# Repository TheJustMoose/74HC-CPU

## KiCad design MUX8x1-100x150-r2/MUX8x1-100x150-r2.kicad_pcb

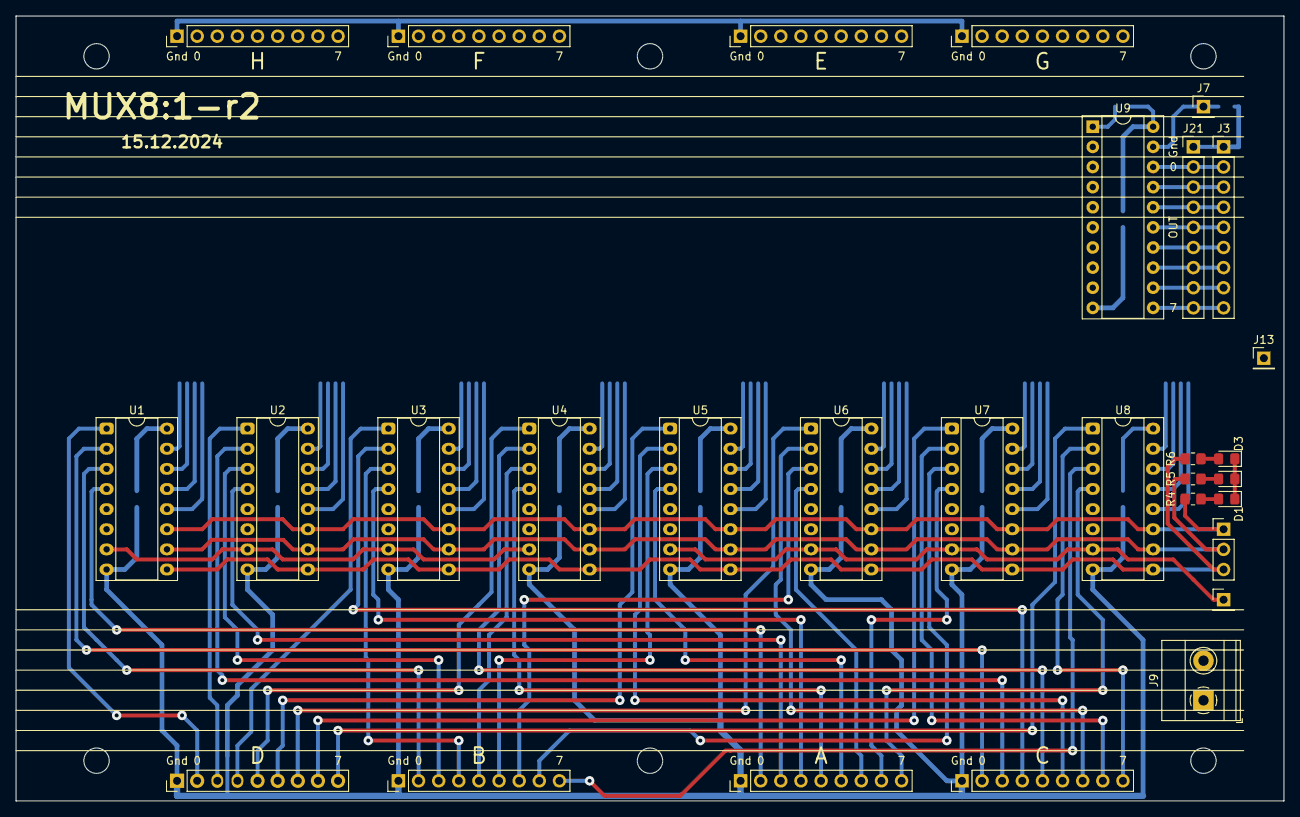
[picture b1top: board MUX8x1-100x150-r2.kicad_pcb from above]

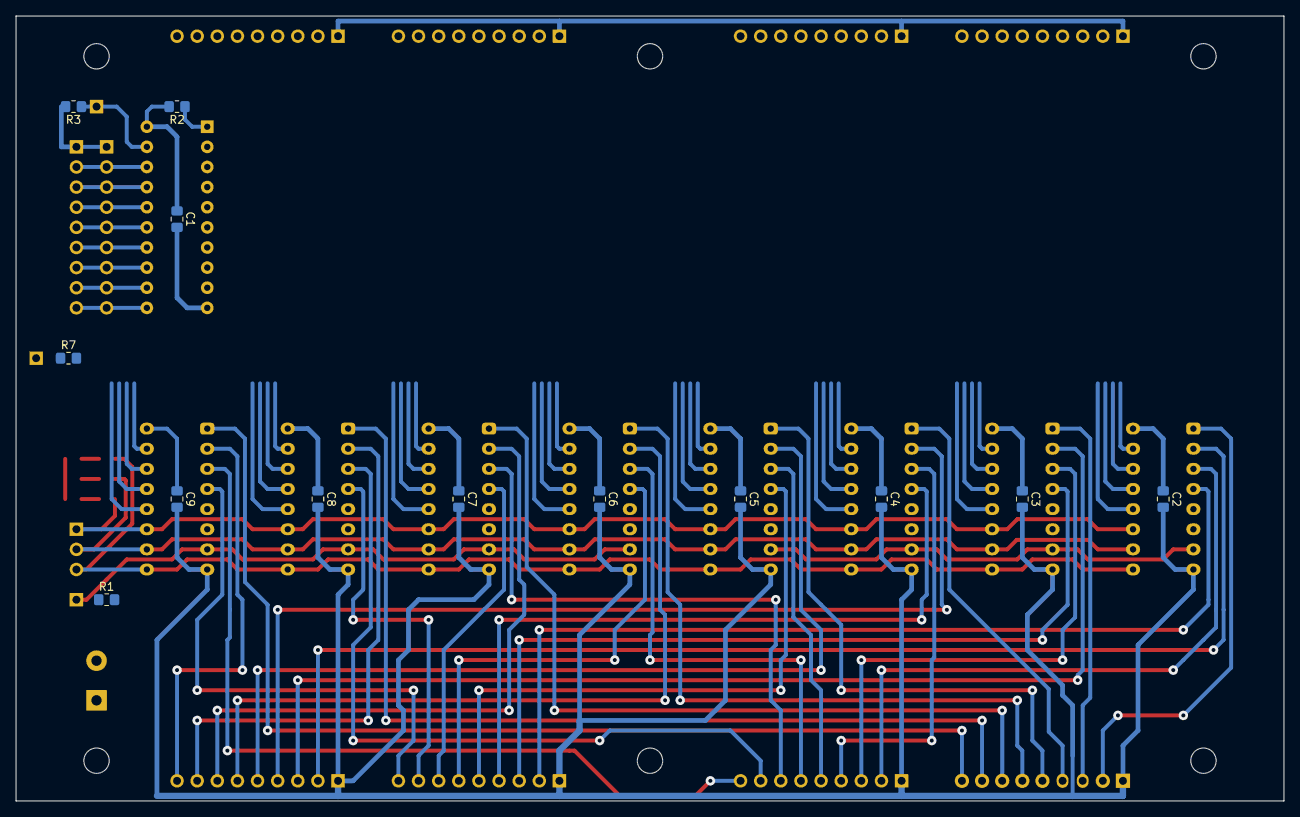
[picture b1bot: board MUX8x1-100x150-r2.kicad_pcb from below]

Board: 2 copper layers, 160.0 x 99.1 mm, 49 parts (13 on the bottom side), 92 nets.

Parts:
C1, C2, C3, C4, C5, C6, C7, C8, C9: 0.1uF; C_0805_2012Metric_Pad1.18x1.45mm_HandSolder
D1, D2, D3: LED; LED_0805_2012Metric_Pad1.15x1.40mm_HandSolder
H1, H2, H3, H4, H5, H6: MountingHole; MountingHole_3.2mm_M3
J1, J2, J3, J5, J6, J11, J12, J15, J16, J21: Conn_01x09_Male; PinHeader_1x09_P2.54mm_Vertical
J7, J13, J20: Conn_01x01_Male; PinHeader_1x01_P2.54mm_Vertical
J9: Screw_Terminal_01x02; TerminalBlock_Phoenix_MKDS-1,5-2_1x02_P5.00mm_Horizontal
J10: Conn_01x03_Male; PinHeader_1x03_P2.54mm_Vertical
R1, R2, R3, R7: 10k; R_0805_2012Metric_Pad1.20x1.40mm_HandSolder
R4, R5, R6: 1k; R_0805_2012Metric_Pad1.20x1.40mm_HandSolder
U1, U2, U3, U4, U5, U6, U7, U8: 74LS151; DIP-16_W7.62mm_Socket
U9: 74HC245; DIP-20_W7.62mm_Socket

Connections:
/A0: J1.2, U1.4
/A1: J1.3, U2.4
/A2: J1.4, U3.4
/A3: J1.5, U4.4
/A4: J1.6, U5.4
/A5: J1.7, U6.4
/A6: J1.8, U7.4
/A7: J1.9, U8.4
/B0: J5.2, U1.3
/B1: J5.3, U2.3
/B2: J5.4, U3.3
/B3: J5.5, U4.3
/B4: J5.6, U5.3
/B5: J5.7, U6.3
/B6: J5.8, U7.3
/B7: J5.9, U8.3
/BUS0: J3.2, J21.2, U9.18
/BUS1: J3.3, J21.3, U9.17
/BUS2: J3.4, J21.4, U9.16
/BUS3: J3.5, J21.5, U9.15
/BUS4: J3.6, J21.6, U9.14
/BUS5: J3.7, J21.7, U9.13
/BUS6: J3.8, J21.8, U9.12
/BUS7: J3.9, J21.9, U9.11
/C0: J11.2, U1.2
/C1: J11.3, U2.2
/C2: J11.4, U3.2
/C3: J11.5, U4.2
/C4: J11.6, U5.2
/C5: J11.7, U6.2
/C6: J11.8, U7.2
/C7: J11.9, U8.2
/D0: J15.2, U1.1
/D1: J15.3, U2.1
/D2: J15.4, U3.1
/D3: J15.5, U4.1
/D4: J15.6, U5.1
/D5: J15.7, U6.1
/D6: J15.8, U7.1
/D7: J15.9, U8.1
/E0: J2.2, U1.15
/E1: J2.3, U2.15
/E2: J2.4, U3.15
/E3: J2.5, U4.15
/E4: J2.6, U5.15
/E5: J2.7, U6.15
/E6: J2.8, U7.15
/E7: J2.9, U8.15
/F0: J6.2, U1.14
/F1: J6.3, U2.14
/F2: J6.4, U3.14
/F3: J6.5, U4.14
/F4: J6.6, U5.14
/F5: J6.7, U6.14
/F6: J6.8, U7.14
/F7: J6.9, U8.14
/G0: J12.2, U1.13
/G1: J12.3, U2.13
/G2: J12.4, U3.13
/G3: J12.5, U4.13
/G4: J12.6, U5.13
/G5: J12.7, U6.13
/G6: J12.8, U7.13
/G7: J12.9, U8.13
/H0: J16.2, U1.12
/H1: J16.3, U2.12
/H2: J16.4, U3.12
/H3: J16.5, U4.12
/H4: J16.6, U5.12
/H5: J16.7, U6.12
/H6: J16.8, U7.12
/H7: J16.9, U8.12
/O0: U1.5, U9.2
/O1: U2.5, U9.3
/O2: U3.5, U9.4
/O3: U4.5, U9.5
/O4: U5.5, U9.6
/O5: U6.5, U9.7
/O6: U7.5, U9.8
/O7: U8.5, U9.9
/S0: J10.1, R4.2, U1.11, U2.11, U3.11, U4.11, U5.11, U6.11, U7.11, U8.11
/S1: J10.2, R5.2, U1.10, U2.10, U3.10, U4.10, U5.10, U6.10, U7.10, U8.10
/S2: J10.3, R6.2, U1.9, U2.9, U3.9, U4.9, U5.9, U6.9, U7.9, U8.9
/~EH: J20.1, R1.1, U5.7, U6.7, U7.7, U8.7
/~EL: J13.1, R7.1, U1.7, U2.7, U3.7, U4.7
/~OE: J7.1, R3.1, U9.19
GND: C1.2, C2.2, C3.2, C4.2, C5.2, C6.2, C7.2, C8.2, C9.2, D1.1, D2.1, D3.1, J1.1, J2.1, J3.1, J5.1, J6.1, J9.2, J11.1, J12.1, J15.1, J16.1, J21.1, R1.2, R3.2, R7.2, U1.8, U2.8, U3.8, U4.8, U5.8, U6.8, U7.8, U8.8, U9.10
unnamed: D1.2, R4.1
unnamed: D2.2, R5.1
unnamed: D3.2, R6.1
unnamed: R2.1, U9.1
VCC: C1.1, C2.1, C3.1, C4.1, C5.1, C6.1, C7.1, C8.1, C9.1, J9.1, R2.2, U1.16, U2.16, U3.16, U4.16, U5.16, U6.16, U7.16, U8.16, U9.20

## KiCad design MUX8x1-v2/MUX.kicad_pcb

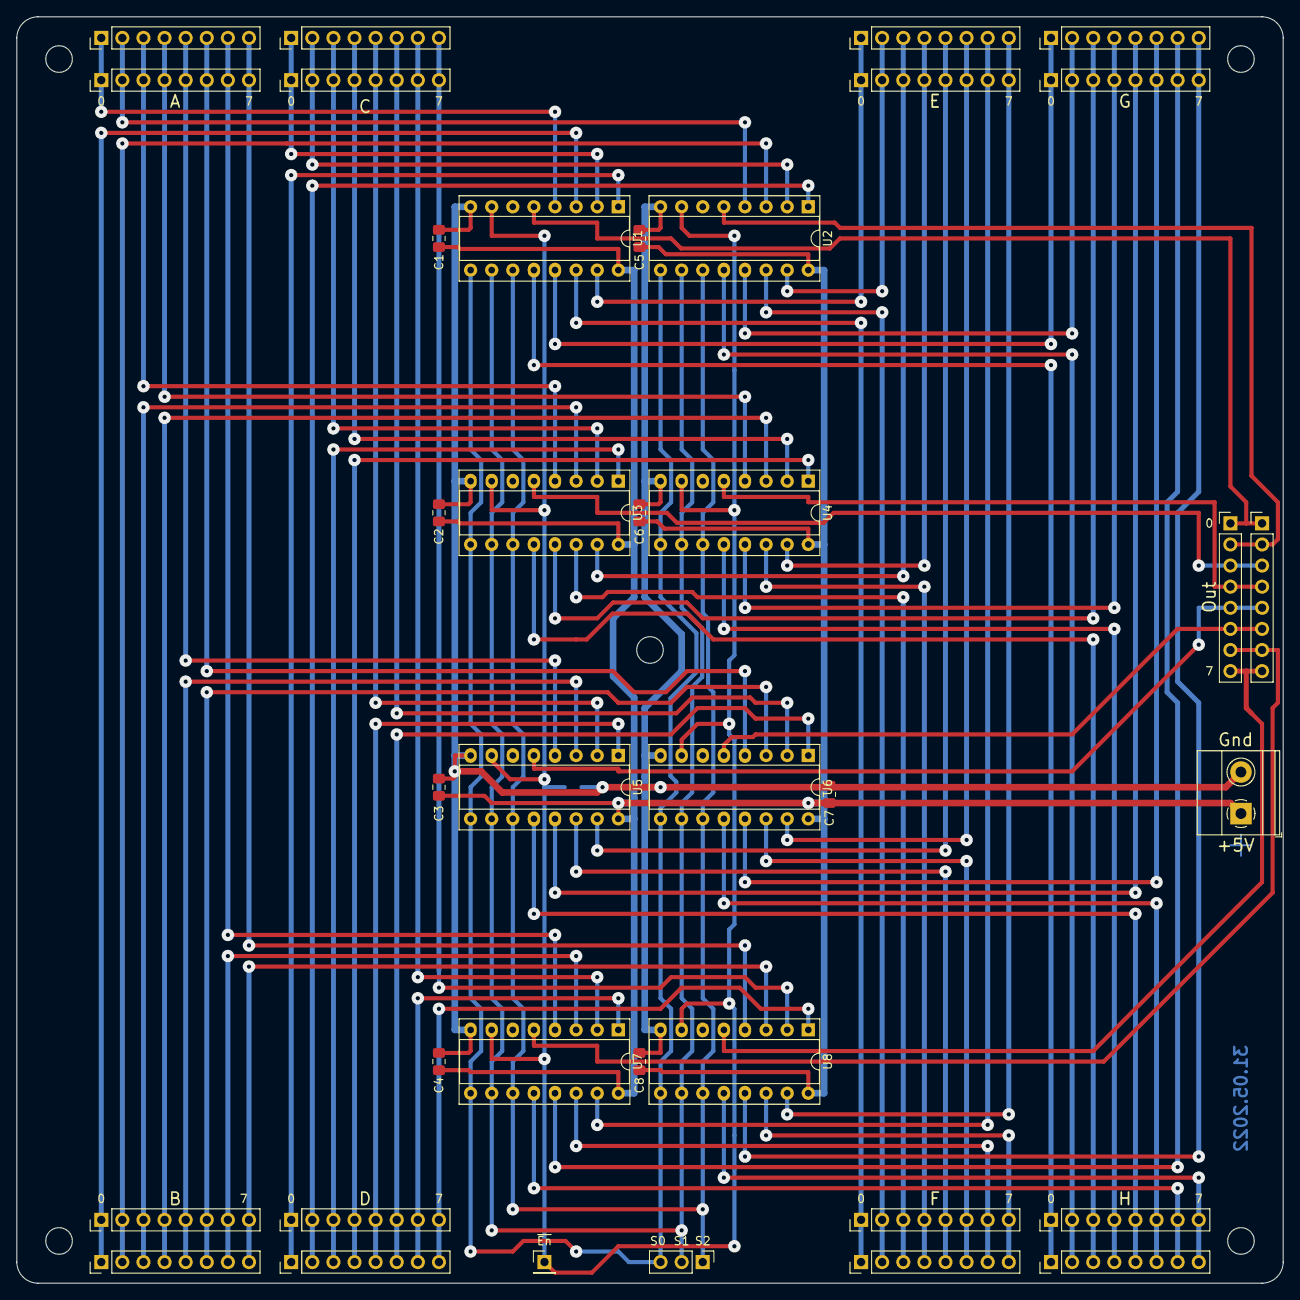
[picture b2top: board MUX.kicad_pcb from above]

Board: 2 copper layers, 152.4 x 152.4 mm, 43 parts (1 on the bottom side), 78 nets.

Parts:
C1, C2, C3, C4, C5, C6, C7, C8: 0.1uF; C_0805_2012Metric_Pad1.18x1.45mm_HandSolder
H1, H2, H3, H4, H5: MountingHole; MountingHole_3.2mm_M3
J1, J2, J3, J4, J5, J6, J7, J8, J11, J12, J13, J14, J15, J16, J17, J18, J19, J21: Conn_01x08_Male; PinHeader_1x08_P2.54mm_Vertical
J9: Screw_Terminal_01x02; TerminalBlock_Phoenix_MKDS-1,5-2_1x02_P5.00mm_Horizontal
J10: Conn_01x03_Male; PinHeader_1x03_P2.54mm_Vertical
J20: Conn_01x01_Male; PinHeader_1x01_P2.54mm_Vertical
R1: 10k; R_0805_2012Metric_Pad1.20x1.40mm_HandSolder
U1, U2, U3, U4, U5, U6, U7, U8: 74LS151; DIP-16_W7.62mm_Socket

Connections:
/A0: J1.1, J12.1, U1.4
/A1: J1.2, J12.2, U2.4
/A2: J1.3, J12.3, U3.4
/A3: J1.4, J12.4, U4.4
/A4: J1.5, J12.5, U5.4
/A5: J1.6, J12.6, U6.4
/A6: J1.7, J12.7, U7.4
/A7: J1.8, J12.8, U8.4
/B0: J3.1, J14.1, U1.3
/B1: J3.2, J14.2, U2.3
/B2: J3.3, J14.3, U3.3
/B3: J3.4, J14.4, U4.3
/B4: J3.5, J14.5, U5.3
/B5: J3.6, J14.6, U6.3
/B6: J3.7, J14.7, U7.3
/B7: J3.8, J14.8, U8.3
/C0: J5.1, J16.1, U1.2
/C1: J5.2, J16.2, U2.2
/C2: J5.3, J16.3, U3.2
/C3: J5.4, J16.4, U4.2
/C4: J5.5, J16.5, U5.2
/C5: J5.6, J16.6, U6.2
/C6: J5.7, J16.7, U7.2
/C7: J5.8, J16.8, U8.2
/D0: J7.1, J18.1, U1.1
/D1: J7.2, J18.2, U2.1
/D2: J7.3, J18.3, U3.1
/D3: J7.4, J18.4, U4.1
/D4: J7.5, J18.5, U5.1
/D5: J7.6, J18.6, U6.1
/D6: J7.7, J18.7, U7.1
/D7: J7.8, J18.8, U8.1
/E0: J2.1, J13.1, U1.15
/E1: J2.2, J13.2, U2.15
/E2: J2.3, J13.3, U3.15
/E3: J2.4, J13.4, U4.15
/E4: J2.5, J13.5, U5.15
/E5: J2.6, J13.6, U6.15
/E6: J2.7, J13.7, U7.15
/E7: J2.8, J13.8, U8.15
/F0: J4.1, J15.1, U1.14
/F1: J4.2, J15.2, U2.14
/F2: J4.3, J15.3, U3.14
/F3: J4.4, J15.4, U4.14
/F4: J4.5, J15.5, U5.14
/F5: J4.6, J15.6, U6.14
/F6: J4.7, J15.7, U7.14
/F7: J4.8, J15.8, U8.14
/G0: J6.1, J17.1, U1.13
/G1: J6.2, J17.2, U2.13
/G2: J6.3, J17.3, U3.13
/G3: J6.4, J17.4, U4.13
/G4: J6.5, J17.5, U5.13
/G5: J6.6, J17.6, U6.13
/G6: J6.7, J17.7, U7.13
/G7: J6.8, J17.8, U8.13
/H0: J8.1, J19.1, U1.12
/H1: J8.2, J19.2, U2.12
/H2: J8.3, J19.3, U3.12
/H3: J8.4, J19.4, U4.12
/H4: J8.5, J19.5, U5.12
/H5: J8.6, J19.6, U6.12
/H6: J8.7, J19.7, U7.12
/H7: J8.8, J19.8, U8.12
/O0: J11.1, J21.1, U1.5
/O1: J11.2, J21.2, U2.5
/O2: J11.3, J21.3, U3.5
/O3: J11.4, J21.4, U4.5
/O4: J11.5, J21.5, U5.5
/O5: J11.6, J21.6, U6.5
/O6: J11.7, J21.7, U7.5
/O7: J11.8, J21.8, U8.5
/S0: J10.1, U1.11, U2.11, U3.11, U4.11, U5.11, U6.11, U7.11, U8.11
/S1: J10.2, U1.10, U2.10, U3.10, U4.10, U5.10, U6.10, U7.10, U8.10
/S2: J10.3, U1.9, U2.9, U3.9, U4.9, U5.9, U6.9, U7.9, U8.9
/~E: J20.1, R1.1, U1.7, U2.7, U3.7, U4.7, U5.7, U6.7, U7.7, U8.7
GND: C1.2, C2.2, C3.2, C4.2, C5.2, C6.2, C7.2, C8.2, J9.2, R1.2, U1.8, U2.8, U3.8, U4.8, U5.8, U6.8, U7.8, U8.8
VCC: C1.1, C2.1, C3.1, C4.1, C5.1, C6.1, C7.1, C8.1, J9.1, U1.16, U2.16, U3.16, U4.16, U5.16, U6.16, U7.16, U8.16
